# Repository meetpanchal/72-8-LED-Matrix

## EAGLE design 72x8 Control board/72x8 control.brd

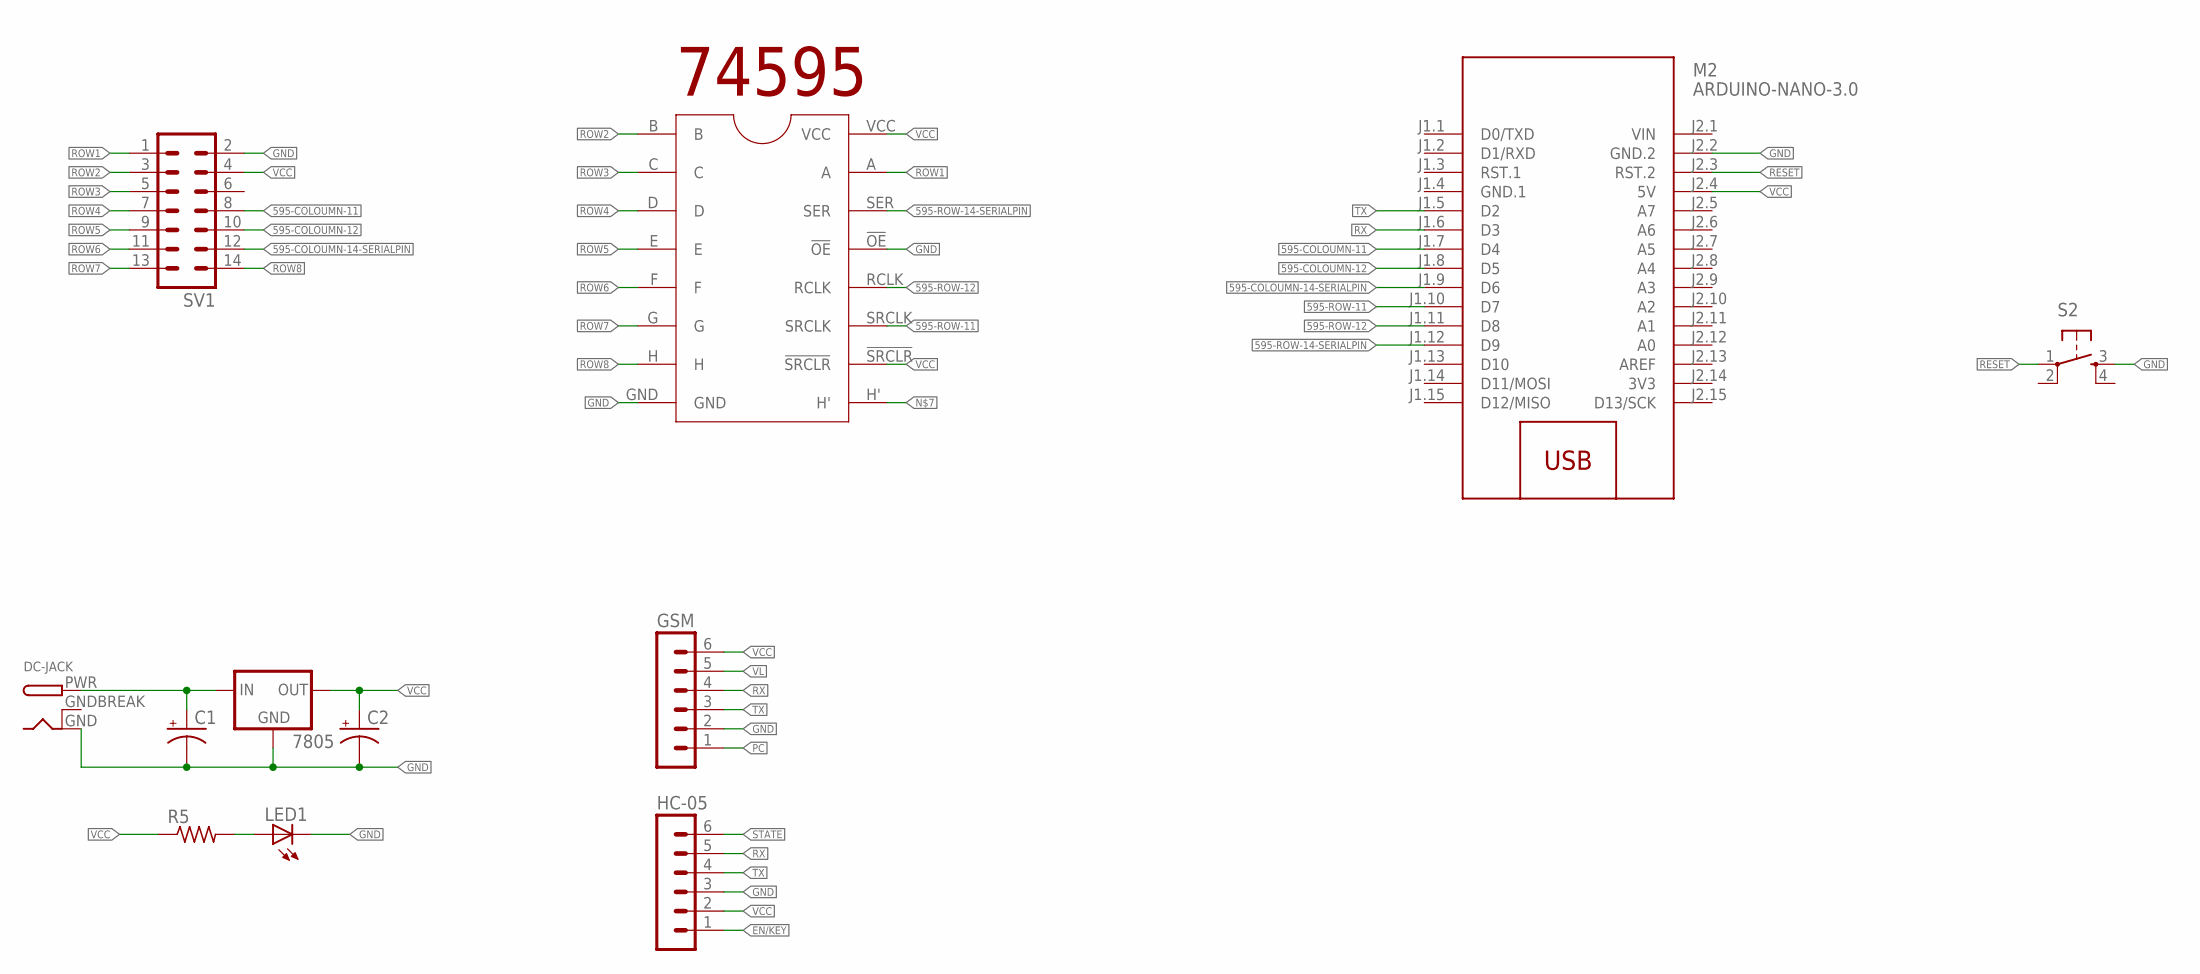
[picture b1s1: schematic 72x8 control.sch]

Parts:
1: 74595; DIL16
7805: 78XX-TO3; TO3-78
C1, C2: CPOL-USE2-5; E2-5
DC-JACK: DCBARRELPTH; DCJACK_2MM_PTH
GSM: MA06-1
HC-05: MA06-1
LED1: LED5MM
M2: ARDUINO-NANO-3.0
R5: R-US_0207/10; 0207/10
S2: TAC_SWITCHPTH; TACTILE-PTH
SV1: MA07-2

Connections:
3V3: M2.J2.14 (3V3)
12V: 7805.2 (IN), C1.+, DC-JACK.PWR
595-COLOUMN-11: M2.J1.7 (D4), SV1.8
595-COLOUMN-12: M2.J1.8 (D5), SV1.10
595-COLOUMN-14-SERIALPIN: M2.J1.9 (D6), SV1.12
595-ROW-11: 1.SRCLK, M2.J1.10 (D7)
595-ROW-12: 1.RCLK, M2.J1.11 (D8)
595-ROW-14-SERIALPIN: 1.SER, M2.J1.12 (D9)
EN/KEY: HC-05.1
GND: 1.!OE, 1.GND, 7805.3 (GND), C1.-, C2.-, DC-JACK.GND, GSM.2, HC-05.3, LED1.K (C), M2.J2.2 (GND.2), S2.3, SV1.2
GND.1: M2.J1.4 (GND.1)
GNDBREAK: DC-JACK.GNDBREAK
unnamed: LED1.A, R5.2
PC: GSM.1
RESET: M2.J2.3 (RST.2), S2.1
ROW1: 1.A, SV1.1
ROW2: 1.B, SV1.3
ROW3: 1.C, SV1.5
ROW4: 1.D, SV1.7
ROW5: 1.E, SV1.9
ROW6: 1.F, SV1.11
ROW7: 1.G, SV1.13
ROW8: 1.H, SV1.14
RX: GSM.4, HC-05.5, M2.J1.6 (D3)
STATE: HC-05.6
TX: GSM.3, HC-05.4, M2.J1.5 (D2)
VCC: 1.!SRCLR, 1.VCC, 7805.1 (OUT), C2.+, GSM.6, HC-05.2, M2.J2.4 (5V), R5.1, SV1.4
VIN: M2.J2.1 (VIN)
VL: GSM.5

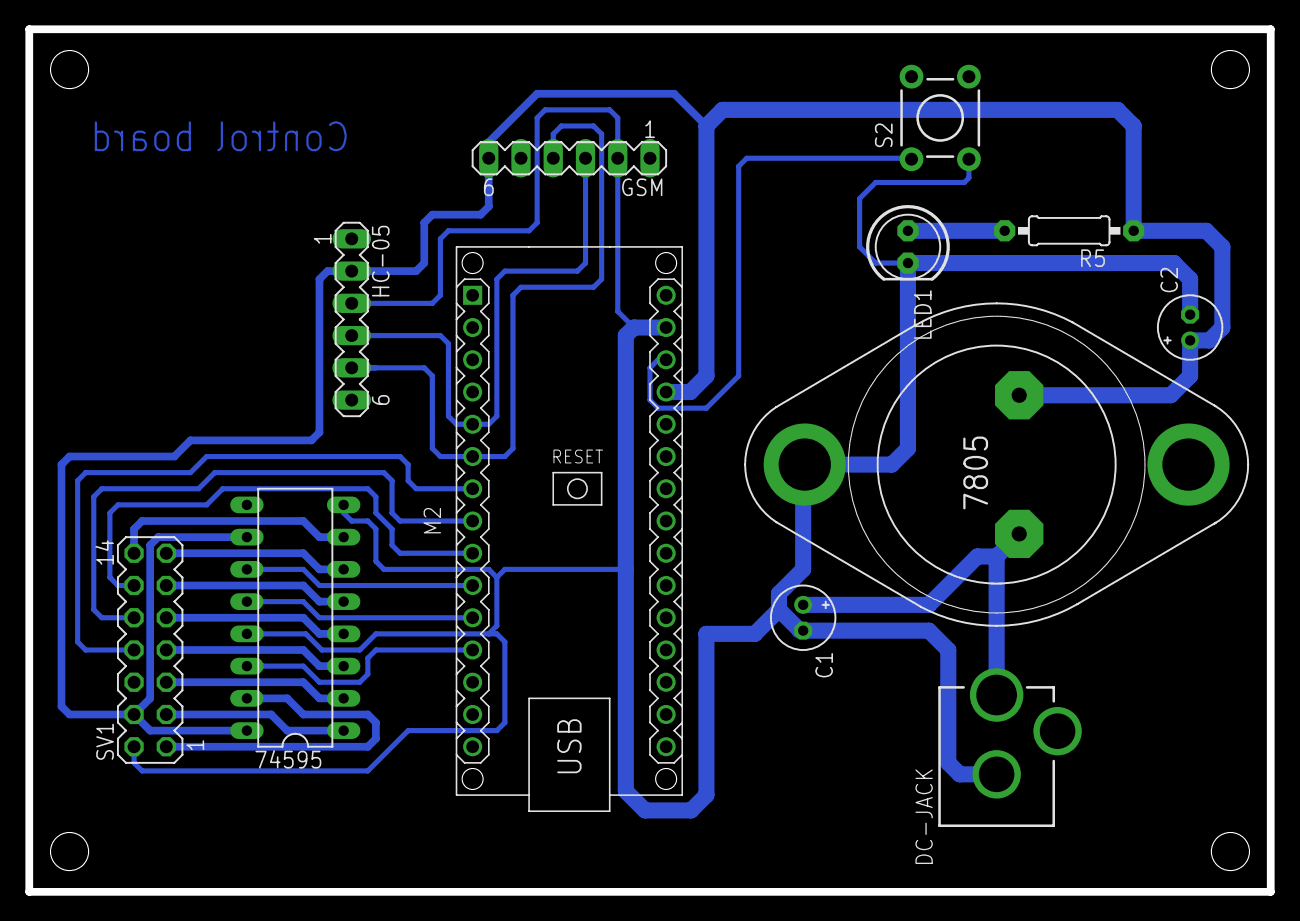
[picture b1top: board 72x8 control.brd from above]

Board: 2 copper layers, 97.8 x 67.9 mm, 12 parts (0 on the bottom side), 21 nets.

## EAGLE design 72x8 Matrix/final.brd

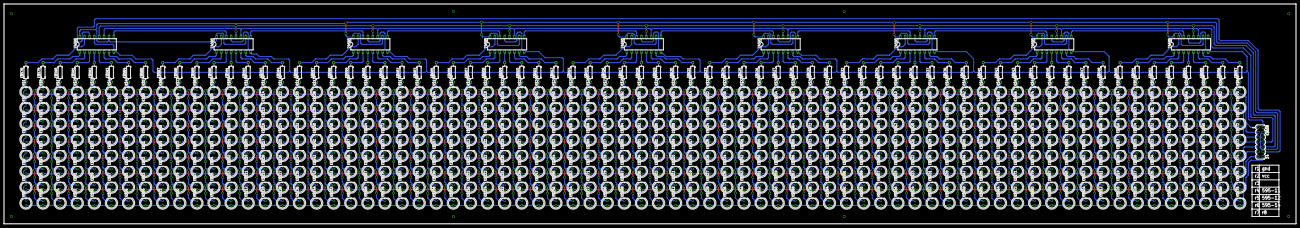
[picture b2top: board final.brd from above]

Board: 2 copper layers, 671.8 x 114.3 mm, 658 parts (0 on the bottom side), 165 nets.

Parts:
E$1, E$2, E$3, E$4, E$5, E$6, E$7, E$8, E$9, E$10, E$11, E$12, E$13, E$14, E$15, E$16, E$17, E$18, E$19, E$20, E$21, E$22, E$23, E$24, E$25, E$26, E$27, E$28, E$29, E$30, E$31, E$32, E$33, E$34, E$35, E$36, E$37, E$38, E$39, E$40, E$41, E$42, E$43, E$44, E$45, E$46, E$47, E$48, E$49, E$50, E$51, E$52, E$53, E$54, E$55, E$56, E$57, E$58, E$59, E$60, E$61, E$62, E$63, E$64, E$65, E$66, E$67, E$68, E$69, E$70, E$71, E$72, E$73, E$74, E$75, E$76, E$77, E$78, E$79, E$80, E$81, E$82, E$83, E$84, E$85, E$86, E$87, E$88, E$89, E$90, E$91, E$92, E$93, E$94, E$95, E$96, E$97, E$98, E$99, E$100, E$101, E$102, E$103, E$104, E$105, E$106, E$107, E$108, E$109, E$110, E$111, E$112, E$113, E$114, E$115, E$116, E$117, E$118, E$119, E$120, E$121, E$122, E$123, E$124, E$125, E$126, E$127, E$128, E$129, E$130, E$131, E$132, E$133, E$134, E$135, E$136, E$137, E$138, E$139, E$140, E$141, E$142, E$143, E$144, E$145, E$146, E$147, E$148, E$149, E$150, E$151, E$152, E$153, E$154, E$155, E$156, E$157, E$158, E$159, E$160, E$161, E$162, E$163, E$164, E$165, E$166, E$167, E$168, E$169, E$170, E$171, E$172, E$173, E$174, E$175, E$176, E$177, E$178, E$179, E$180, E$181, E$182, E$183, E$184, E$185, E$186, E$187, E$188, E$189, E$190, E$191, E$192, E$193, E$194, E$195, E$196, E$197, E$198, E$199, E$200, E$201, E$202, E$203, E$204, E$205, E$206, E$207, E$208, E$209, E$210, E$211, E$212, E$213, E$214, E$215, E$216, E$217, E$218, E$219, E$220, E$221, E$222, E$223, E$224, E$225, E$226, E$227, E$228, E$229, E$230, E$231, E$232, E$233, E$234, E$235, E$236, E$237, E$238, E$239, E$240, E$241, E$242, E$243, E$244, E$245, E$246, E$247, E$248, E$249, E$250, E$251, E$252, E$253, E$254, E$255, E$256, E$257, E$258, E$259, E$260, E$261, E$262, E$263, E$264, E$265, E$266, E$267, E$268, E$269, E$270, E$271, E$272, E$273, E$274, E$275, E$276, E$277, E$278, E$279, E$280, E$281, E$282, E$283, E$284, E$285, E$286, E$287, E$288, E$289, E$290, E$291, E$292, E$293, E$294, E$295, E$296, E$297, E$298, E$299, E$300, E$301, E$302, E$303, E$304, E$305, E$306, E$307, E$308, E$309, E$310, E$311, E$312, E$313, E$314, E$315, E$316, E$317, E$318, E$319, E$320, E$321, E$322, E$323, E$324, E$325, E$326, E$327, E$328, E$329, E$330, E$331, E$332, E$333, E$334, E$335, E$336, E$337, E$338, E$339, E$340, E$341, E$342, E$343, E$344, E$345, E$346, E$347, E$348, E$349, E$350, E$351, E$352, E$353, E$354, E$355, E$356, E$357, E$358, E$359, E$360, E$361, E$362, E$363, E$364, E$365, E$366, E$367, E$368, E$369, E$370, E$371, E$372, E$373, E$374, E$375, E$376, E$377, E$378, E$379, E$380, E$381, E$382, E$383, E$384, E$385, E$386, E$387, E$388, E$389, E$390, E$391, E$392, E$393, E$394, E$395, E$396, E$397, E$398, E$399, E$400, E$401, E$402, E$403, E$404, E$405, E$406, E$407, E$408, E$409, E$410, E$411, E$412, E$413, E$414, E$415, E$416, E$417, E$418, E$419, E$420, E$421, E$422, E$423, E$424, E$425, E$426, E$427, E$428, E$429, E$430, E$431, E$432, E$433, E$434, E$435, E$436, E$437, E$438, E$439, E$440, E$441, E$442, E$443, E$444, E$445, E$446, E$447, E$448, E$449, E$450, E$451, E$452, E$453, E$454, E$455, E$456, E$457, E$458, E$459, E$460, E$461, E$462, E$463, E$464, E$465, E$466, E$467, E$468, E$469, E$470, E$471, E$472, E$473, E$474, E$475, E$476, E$477, E$478, E$479, E$480, E$481, E$482, E$483, E$484, E$485, E$486, E$487, E$488, E$489, E$490, E$491, E$492, E$493, E$494, E$495, E$496, E$497, E$498, E$499, E$500, E$501, E$502, E$503, E$504, E$505, E$506, E$507, E$508, E$509, E$510, E$511, E$512, E$513, E$514, E$515, E$516, E$517, E$518, E$519, E$520, E$521, E$522, E$523, E$524, E$525, E$526, E$527, E$528, E$529, E$530, E$531, E$532, E$533, E$534, E$535, E$536, E$537, E$538, E$539, E$540, E$541, E$542, E$543, E$544, E$545, E$546, E$547, E$548, E$549, E$550, E$551, E$552, E$553, E$554, E$555, E$556, E$557, E$558, E$559, E$560, E$561, E$562, E$563, E$564, E$565, E$566, E$567, E$568, E$569, E$570, E$571, E$572, E$573, E$574, E$575, E$576: LED5MM
E$577, E$586, E$595, E$604, E$613, E$622, E$631, E$640, E$649: DIL16
E$578, E$579, E$580, E$581, E$582, E$583, E$584, E$585, E$587, E$588, E$589, E$590, E$591, E$592, E$593, E$594, E$596, E$597, E$598, E$599, E$600, E$601, E$602, E$603, E$605, E$606, E$607, E$608, E$609, E$610, E$611, E$612, E$614, E$615, E$616, E$617, E$618, E$619, E$620, E$621, E$623, E$624, E$625, E$626, E$627, E$628, E$629, E$630, E$632, E$633, E$634, E$635, E$636, E$637, E$638, E$639, E$641, E$642, E$643, E$644, E$645, E$646, E$647, E$648, E$650, E$651, E$652, E$653, E$654, E$655, E$656, E$657: 0207/10
E$658: MA07-2

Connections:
595-11: E$577.SRCLK, E$586.SRCLK, E$595.SRCLK, E$604.SRCLK, E$613.SRCLK, E$622.SRCLK, E$631.SRCLK, E$640.SRCLK, E$649.SRCLK, E$658.8
595-12: E$577.RCLK, E$586.RCLK, E$595.RCLK, E$604.RCLK, E$613.RCLK, E$622.RCLK, E$631.RCLK, E$640.RCLK, E$649.RCLK, E$658.10
595-(14)-SERIALPIN: E$577.SER, E$658.12
GND: E$577.!OE, E$577.GND, E$586.!OE, E$586.GND, E$595.!OE, E$595.GND, E$604.!OE, E$604.GND, E$613.!OE, E$613.GND, E$622.!OE, E$622.GND, E$631.!OE, E$631.GND, E$640.!OE, E$640.GND, E$649.!OE, E$649.GND, E$658.2
ROW1: E$1.A, E$9.A, E$17.A, E$25.A, E$33.A, E$41.A, E$49.A, E$57.A, E$65.A, E$73.A, E$81.A, E$89.A, E$97.A, E$105.A, E$113.A, E$121.A, E$129.A, E$137.A, E$145.A, E$153.A, E$161.A, E$169.A, E$177.A, E$185.A, E$193.A, E$201.A, E$209.A, E$217.A, E$225.A, E$233.A, E$241.A, E$249.A, E$257.A, E$265.A, E$273.A, E$281.A, E$289.A, E$297.A, E$305.A, E$313.A, E$321.A, E$329.A, E$337.A, E$345.A, E$353.A, E$361.A, E$369.A, E$377.A, E$385.A, E$393.A, E$401.A, E$409.A, E$417.A, E$425.A, E$433.A, E$441.A, E$449.A, E$457.A, E$465.A, E$473.A, E$481.A, E$489.A, E$497.A, E$505.A, E$513.A, E$521.A, E$529.A, E$537.A, E$545.A, E$553.A, E$561.A, E$569.A, E$658.1
ROW2: E$2.A, E$10.A, E$18.A, E$26.A, E$34.A, E$42.A, E$50.A, E$58.A, E$66.A, E$74.A, E$82.A, E$90.A, E$98.A, E$106.A, E$114.A, E$122.A, E$130.A, E$138.A, E$146.A, E$154.A, E$162.A, E$170.A, E$178.A, E$186.A, E$194.A, E$202.A, E$210.A, E$218.A, E$226.A, E$234.A, E$242.A, E$250.A, E$258.A, E$266.A, E$274.A, E$282.A, E$290.A, E$298.A, E$306.A, E$314.A, E$322.A, E$330.A, E$338.A, E$346.A, E$354.A, E$362.A, E$370.A, E$378.A, E$386.A, E$394.A, E$402.A, E$410.A, E$418.A, E$426.A, E$434.A, E$442.A, E$450.A, E$458.A, E$466.A, E$474.A, E$482.A, E$490.A, E$498.A, E$506.A, E$514.A, E$522.A, E$530.A, E$538.A, E$546.A, E$554.A, E$562.A, E$570.A, E$658.3
ROW3: E$3.A, E$11.A, E$19.A, E$27.A, E$35.A, E$43.A, E$51.A, E$59.A, E$67.A, E$75.A, E$83.A, E$91.A, E$99.A, E$107.A, E$115.A, E$123.A, E$131.A, E$139.A, E$147.A, E$155.A, E$163.A, E$171.A, E$179.A, E$187.A, E$195.A, E$203.A, E$211.A, E$219.A, E$227.A, E$235.A, E$243.A, E$251.A, E$259.A, E$267.A, E$275.A, E$283.A, E$291.A, E$299.A, E$307.A, E$315.A, E$323.A, E$331.A, E$339.A, E$347.A, E$355.A, E$363.A, E$371.A, E$379.A, E$387.A, E$395.A, E$403.A, E$411.A, E$419.A, E$427.A, E$435.A, E$443.A, E$451.A, E$459.A, E$467.A, E$475.A, E$483.A, E$491.A, E$499.A, E$507.A, E$515.A, E$523.A, E$531.A, E$539.A, E$547.A, E$555.A, E$563.A, E$571.A, E$658.5
ROW4: E$4.A, E$12.A, E$20.A, E$28.A, E$36.A, E$44.A, E$52.A, E$60.A, E$68.A, E$76.A, E$84.A, E$92.A, E$100.A, E$108.A, E$116.A, E$124.A, E$132.A, E$140.A, E$148.A, E$156.A, E$164.A, E$172.A, E$180.A, E$188.A, E$196.A, E$204.A, E$212.A, E$220.A, E$228.A, E$236.A, E$244.A, E$252.A, E$260.A, E$268.A, E$276.A, E$284.A, E$292.A, E$300.A, E$308.A, E$316.A, E$324.A, E$332.A, E$340.A, E$348.A, E$356.A, E$364.A, E$372.A, E$380.A, E$388.A, E$396.A, E$404.A, E$412.A, E$420.A, E$428.A, E$436.A, E$444.A, E$452.A, E$460.A, E$468.A, E$476.A, E$484.A, E$492.A, E$500.A, E$508.A, E$516.A, E$524.A, E$532.A, E$540.A, E$548.A, E$556.A, E$564.A, E$572.A, E$658.7
ROW5: E$5.A, E$13.A, E$21.A, E$29.A, E$37.A, E$45.A, E$53.A, E$61.A, E$69.A, E$77.A, E$85.A, E$93.A, E$101.A, E$109.A, E$117.A, E$125.A, E$133.A, E$141.A, E$149.A, E$157.A, E$165.A, E$173.A, E$181.A, E$189.A, E$197.A, E$205.A, E$213.A, E$221.A, E$229.A, E$237.A, E$245.A, E$253.A, E$261.A, E$269.A, E$277.A, E$285.A, E$293.A, E$301.A, E$309.A, E$317.A, E$325.A, E$333.A, E$341.A, E$349.A, E$357.A, E$365.A, E$373.A, E$381.A, E$389.A, E$397.A, E$405.A, E$413.A, E$421.A, E$429.A, E$437.A, E$445.A, E$453.A, E$461.A, E$469.A, E$477.A, E$485.A, E$493.A, E$501.A, E$509.A, E$517.A, E$525.A, E$533.A, E$541.A, E$549.A, E$557.A, E$565.A, E$573.A, E$658.9
ROW6: E$6.A, E$14.A, E$22.A, E$30.A, E$38.A, E$46.A, E$54.A, E$62.A, E$70.A, E$78.A, E$86.A, E$94.A, E$102.A, E$110.A, E$118.A, E$126.A, E$134.A, E$142.A, E$150.A, E$158.A, E$166.A, E$174.A, E$182.A, E$190.A, E$198.A, E$206.A, E$214.A, E$222.A, E$230.A, E$238.A, E$246.A, E$254.A, E$262.A, E$270.A, E$278.A, E$286.A, E$294.A, E$302.A, E$310.A, E$318.A, E$326.A, E$334.A, E$342.A, E$350.A, E$358.A, E$366.A, E$374.A, E$382.A, E$390.A, E$398.A, E$406.A, E$414.A, E$422.A, E$430.A, E$438.A, E$446.A, E$454.A, E$462.A, E$470.A, E$478.A, E$486.A, E$494.A, E$502.A, E$510.A, E$518.A, E$526.A, E$534.A, E$542.A, E$550.A, E$558.A, E$566.A, E$574.A, E$658.11
ROW7: E$7.A, E$15.A, E$23.A, E$31.A, E$39.A, E$47.A, E$55.A, E$63.A, E$71.A, E$79.A, E$87.A, E$95.A, E$103.A, E$111.A, E$119.A, E$127.A, E$135.A, E$143.A, E$151.A, E$159.A, E$167.A, E$175.A, E$183.A, E$191.A, E$199.A, E$207.A, E$215.A, E$223.A, E$231.A, E$239.A, E$247.A, E$255.A, E$263.A, E$271.A, E$279.A, E$287.A, E$295.A, E$303.A, E$311.A, E$319.A, E$327.A, E$335.A, E$343.A, E$351.A, E$359.A, E$367.A, E$375.A, E$383.A, E$391.A, E$399.A, E$407.A, E$415.A, E$423.A, E$431.A, E$439.A, E$447.A, E$455.A, E$463.A, E$471.A, E$479.A, E$487.A, E$495.A, E$503.A, E$511.A, E$519.A, E$527.A, E$535.A, E$543.A, E$551.A, E$559.A, E$567.A, E$575.A, E$658.13
ROW8: E$8.A, E$16.A, E$24.A, E$32.A, E$40.A, E$48.A, E$56.A, E$64.A, E$72.A, E$80.A, E$88.A, E$96.A, E$104.A, E$112.A, E$120.A, E$128.A, E$136.A, E$144.A, E$152.A, E$160.A, E$168.A, E$176.A, E$184.A, E$192.A, E$200.A, E$208.A, E$216.A, E$224.A, E$232.A, E$240.A, E$248.A, E$256.A, E$264.A, E$272.A, E$280.A, E$288.A, E$296.A, E$304.A, E$312.A, E$320.A, E$328.A, E$336.A, E$344.A, E$352.A, E$360.A, E$368.A, E$376.A, E$384.A, E$392.A, E$400.A, E$408.A, E$416.A, E$424.A, E$432.A, E$440.A, E$448.A, E$456.A, E$464.A, E$472.A, E$480.A, E$488.A, E$496.A, E$504.A, E$512.A, E$520.A, E$528.A, E$536.A, E$544.A, E$552.A, E$560.A, E$568.A, E$576.A, E$658.14
S$1: E$9.K, E$10.K, E$11.K, E$12.K, E$13.K, E$14.K, E$15.K, E$16.K, E$579.1
S$10: E$17.K, E$18.K, E$19.K, E$20.K, E$21.K, E$22.K, E$23.K, E$24.K, E$580.1
S$11: E$1.K, E$2.K, E$3.K, E$4.K, E$5.K, E$6.K, E$7.K, E$8.K, E$578.1
S$12: E$577.A, E$578.2
S$13: E$577.B, E$579.2
S$14: E$577.C, E$580.2
S$15: E$577.D, E$581.2
S$16: E$577.E, E$582.2
S$17: E$577.F, E$583.2
S$18: E$577.G, E$584.2
S$19: E$25.K, E$26.K, E$27.K, E$28.K, E$29.K, E$30.K, E$31.K, E$32.K, E$581.1
S$20: E$41.K, E$42.K, E$43.K, E$44.K, E$45.K, E$46.K, E$47.K, E$48.K, E$583.1
S$21: E$57.K, E$58.K, E$59.K, E$60.K, E$61.K, E$62.K, E$63.K, E$64.K, E$585.1
S$22: E$49.K, E$50.K, E$51.K, E$52.K, E$53.K, E$54.K, E$55.K, E$56.K, E$584.1
S$23: E$33.K, E$34.K, E$35.K, E$36.K, E$37.K, E$38.K, E$39.K, E$40.K, E$582.1
S$24: E$73.K, E$74.K, E$75.K, E$76.K, E$77.K, E$78.K, E$79.K, E$80.K, E$588.1
S$25: E$89.K, E$90.K, E$91.K, E$92.K, E$93.K, E$94.K, E$95.K, E$96.K, E$590.1
S$26: E$81.K, E$82.K, E$83.K, E$84.K, E$85.K, E$86.K, E$87.K, E$88.K, E$589.1
S$27: E$105.K, E$106.K, E$107.K, E$108.K, E$109.K, E$110.K, E$111.K, E$112.K, E$592.1
S$28: E$121.K, E$122.K, E$123.K, E$124.K, E$125.K, E$126.K, E$127.K, E$128.K, E$594.1
S$29: E$113.K, E$114.K, E$115.K, E$116.K, E$117.K, E$118.K, E$119.K, E$120.K, E$593.1
S$30: E$97.K, E$98.K, E$99.K, E$100.K, E$101.K, E$102.K, E$103.K, E$104.K, E$591.1
S$31: E$65.K, E$66.K, E$67.K, E$68.K, E$69.K, E$70.K, E$71.K, E$72.K, E$587.1
S$32: E$137.K, E$138.K, E$139.K, E$140.K, E$141.K, E$142.K, E$143.K, E$144.K, E$597.1
S$33: E$153.K, E$154.K, E$155.K, E$156.K, E$157.K, E$158.K, E$159.K, E$160.K, E$599.1
S$34: E$145.K, E$146.K, E$147.K, E$148.K, E$149.K, E$150.K, E$151.K, E$152.K, E$598.1
S$35: E$169.K, E$170.K, E$171.K, E$172.K, E$173.K, E$174.K, E$175.K, E$176.K, E$601.1
S$36: E$185.K, E$186.K, E$187.K, E$188.K, E$189.K, E$190.K, E$191.K, E$192.K, E$603.1
S$37: E$177.K, E$178.K, E$179.K, E$180.K, E$181.K, E$182.K, E$183.K, E$184.K, E$602.1
S$38: E$161.K, E$162.K, E$163.K, E$164.K, E$165.K, E$166.K, E$167.K, E$168.K, E$600.1
S$39: E$201.K, E$202.K, E$203.K, E$204.K, E$205.K, E$206.K, E$207.K, E$208.K, E$606.1
S$40: E$217.K, E$218.K, E$219.K, E$220.K, E$221.K, E$222.K, E$223.K, E$224.K, E$608.1
S$41: E$209.K, E$210.K, E$211.K, E$212.K, E$213.K, E$214.K, E$215.K, E$216.K, E$607.1
S$42: E$233.K, E$234.K, E$235.K, E$236.K, E$237.K, E$238.K, E$239.K, E$240.K, E$610.1
S$43: E$249.K, E$250.K, E$251.K, E$252.K, E$253.K, E$254.K, E$255.K, E$256.K, E$612.1
S$44: E$241.K, E$242.K, E$243.K, E$244.K, E$245.K, E$246.K, E$247.K, E$248.K, E$611.1
S$45: E$225.K, E$226.K, E$227.K, E$228.K, E$229.K, E$230.K, E$231.K, E$232.K, E$609.1
S$46: E$193.K, E$194.K, E$195.K, E$196.K, E$197.K, E$198.K, E$199.K, E$200.K, E$605.1
S$47: E$129.K, E$130.K, E$131.K, E$132.K, E$133.K, E$134.K, E$135.K, E$136.K, E$596.1
S$48: E$265.K, E$266.K, E$267.K, E$268.K, E$269.K, E$270.K, E$271.K, E$272.K, E$615.1
S$49: E$281.K, E$282.K, E$283.K, E$284.K, E$285.K, E$286.K, E$287.K, E$288.K, E$617.1
S$50: E$273.K, E$274.K, E$275.K, E$276.K, E$277.K, E$278.K, E$279.K, E$280.K, E$616.1
S$51: E$297.K, E$298.K, E$299.K, E$300.K, E$301.K, E$302.K, E$303.K, E$304.K, E$619.1
S$52: E$313.K, E$314.K, E$315.K, E$316.K, E$317.K, E$318.K, E$319.K, E$320.K, E$621.1
S$53: E$305.K, E$306.K, E$307.K, E$308.K, E$309.K, E$310.K, E$311.K, E$312.K, E$620.1
S$54: E$289.K, E$290.K, E$291.K, E$292.K, E$293.K, E$294.K, E$295.K, E$296.K, E$618.1
S$55: E$329.K, E$330.K, E$331.K, E$332.K, E$333.K, E$334.K, E$335.K, E$336.K, E$624.1
S$56: E$345.K, E$346.K, E$347.K, E$348.K, E$349.K, E$350.K, E$351.K, E$352.K, E$626.1
S$57: E$337.K, E$338.K, E$339.K, E$340.K, E$341.K, E$342.K, E$343.K, E$344.K, E$625.1
S$58: E$361.K, E$362.K, E$363.K, E$364.K, E$365.K, E$366.K, E$367.K, E$368.K, E$628.1
S$59: E$377.K, E$378.K, E$379.K, E$380.K, E$381.K, E$382.K, E$383.K, E$384.K, E$630.1
S$60: E$369.K, E$370.K, E$371.K, E$372.K, E$373.K, E$374.K, E$375.K, E$376.K, E$629.1
S$61: E$353.K, E$354.K, E$355.K, E$356.K, E$357.K, E$358.K, E$359.K, E$360.K, E$627.1
S$62: E$321.K, E$322.K, E$323.K, E$324.K, E$325.K, E$326.K, E$327.K, E$328.K, E$623.1
S$63: E$393.K, E$394.K, E$395.K, E$396.K, E$397.K, E$398.K, E$399.K, E$400.K, E$633.1
S$64: E$409.K, E$410.K, E$411.K, E$412.K, E$413.K, E$414.K, E$415.K, E$416.K, E$635.1
S$65: E$401.K, E$402.K, E$403.K, E$404.K, E$405.K, E$406.K, E$407.K, E$408.K, E$634.1
S$66: E$425.K, E$426.K, E$427.K, E$428.K, E$429.K, E$430.K, E$431.K, E$432.K, E$637.1
S$67: E$441.K, E$442.K, E$443.K, E$444.K, E$445.K, E$446.K, E$447.K, E$448.K, E$639.1
S$68: E$433.K, E$434.K, E$435.K, E$436.K, E$437.K, E$438.K, E$439.K, E$440.K, E$638.1
S$69: E$417.K, E$418.K, E$419.K, E$420.K, E$421.K, E$422.K, E$423.K, E$424.K, E$636.1
S$70: E$457.K, E$458.K, E$459.K, E$460.K, E$461.K, E$462.K, E$463.K, E$464.K, E$642.1
S$71: E$473.K, E$474.K, E$475.K, E$476.K, E$477.K, E$478.K, E$479.K, E$480.K, E$644.1
S$72: E$465.K, E$466.K, E$467.K, E$468.K, E$469.K, E$470.K, E$471.K, E$472.K, E$643.1
S$73: E$489.K, E$490.K, E$491.K, E$492.K, E$493.K, E$494.K, E$495.K, E$496.K, E$646.1
S$74: E$505.K, E$506.K, E$507.K, E$508.K, E$509.K, E$510.K, E$511.K, E$512.K, E$648.1
S$75: E$497.K, E$498.K, E$499.K, E$500.K, E$501.K, E$502.K, E$503.K, E$504.K, E$647.1
S$76: E$481.K, E$482.K, E$483.K, E$484.K, E$485.K, E$486.K, E$487.K, E$488.K, E$645.1
S$77: E$449.K, E$450.K, E$451.K, E$452.K, E$453.K, E$454.K, E$455.K, E$456.K, E$641.1
S$78: E$385.K, E$386.K, E$387.K, E$388.K, E$389.K, E$390.K, E$391.K, E$392.K, E$632.1
S$79: E$257.K, E$258.K, E$259.K, E$260.K, E$261.K, E$262.K, E$263.K, E$264.K, E$614.1
S$80: E$521.K, E$522.K, E$523.K, E$524.K, E$525.K, E$526.K, E$527.K, E$528.K, E$651.1
S$81: E$537.K, E$538.K, E$539.K, E$540.K, E$541.K, E$542.K, E$543.K, E$544.K, E$653.1
S$82: E$529.K, E$530.K, E$531.K, E$532.K, E$533.K, E$534.K, E$535.K, E$536.K, E$652.1
S$83: E$553.K, E$554.K, E$555.K, E$556.K, E$557.K, E$558.K, E$559.K, E$560.K, E$655.1
S$84: E$569.K, E$570.K, E$571.K, E$572.K, E$573.K, E$574.K, E$575.K, E$576.K, E$657.1
S$85: E$561.K, E$562.K, E$563.K, E$564.K, E$565.K, E$566.K, E$567.K, E$568.K, E$656.1
S$86: E$545.K, E$546.K, E$547.K, E$548.K, E$549.K, E$550.K, E$551.K, E$552.K, E$654.1
S$87: E$513.K, E$514.K, E$515.K, E$516.K, E$517.K, E$518.K, E$519.K, E$520.K, E$650.1
S$88: E$577.H, E$585.2
S$89: E$586.A, E$587.2
S$90: E$586.B, E$588.2
S$91: E$586.C, E$589.2
S$92: E$586.D, E$590.2
S$93: E$586.E, E$591.2
S$94: E$586.F, E$592.2
S$95: E$586.G, E$593.2
S$96: E$586.H, E$594.2
S$97: E$595.A, E$596.2
S$98: E$595.B, E$597.2
S$99: E$595.C, E$598.2
S$100: E$595.D, E$599.2
S$101: E$595.E, E$600.2
S$102: E$595.F, E$601.2
S$103: E$595.G, E$602.2
S$104: E$595.H, E$603.2
S$105: E$604.A, E$605.2
S$106: E$604.B, E$606.2
S$107: E$604.C, E$607.2
S$108: E$604.D, E$608.2
S$109: E$604.E, E$609.2
S$110: E$604.F, E$610.2
S$111: E$604.G, E$611.2
S$112: E$604.H, E$612.2
S$113: E$613.A, E$614.2
S$114: E$613.B, E$615.2
S$115: E$613.C, E$616.2
S$116: E$613.D, E$617.2
S$117: E$613.E, E$618.2
S$118: E$613.F, E$619.2
S$119: E$613.G, E$620.2
S$120: E$613.H, E$621.2
S$121: E$622.A, E$623.2
S$122: E$622.B, E$624.2
S$123: E$622.C, E$625.2
S$124: E$622.D, E$626.2
S$125: E$622.E, E$627.2
S$126: E$622.F, E$628.2
S$127: E$622.G, E$629.2
S$128: E$622.H, E$630.2
S$129: E$631.A, E$632.2
S$130: E$631.B, E$633.2
S$131: E$631.C, E$634.2
S$132: E$631.D, E$635.2
S$133: E$631.E, E$636.2
S$134: E$631.F, E$637.2
S$135: E$631.G, E$638.2
S$136: E$631.H, E$639.2
S$137: E$640.A, E$641.2
S$138: E$640.B, E$642.2
S$139: E$640.C, E$643.2
S$140: E$640.D, E$644.2
S$141: E$640.E, E$645.2
S$142: E$640.F, E$646.2
S$143: E$640.G, E$647.2
S$144: E$640.H, E$648.2
S$145: E$649.A, E$650.2
S$146: E$649.B, E$651.2
S$147: E$649.C, E$652.2
S$148: E$649.D, E$653.2
S$149: E$649.E, E$654.2
S$150: E$649.F, E$655.2
S$151: E$649.G, E$656.2
S$152: E$649.H, E$657.2
S$155: E$577.H', E$586.SER
S$156: E$586.H', E$595.SER
S$157: E$595.H', E$604.SER
S$158: E$604.H', E$613.SER
S$159: E$613.H', E$622.SER
S$160: E$622.H', E$631.SER
S$161: E$631.H', E$640.SER
S$162: E$640.H', E$649.SER
VCC: E$577.!SRCLR, E$577.VCC, E$586.!SRCLR, E$586.VCC, E$595.!SRCLR, E$595.VCC, E$604.!SRCLR, E$604.VCC, E$613.!SRCLR, E$613.VCC, E$622.!SRCLR, E$622.VCC, E$631.!SRCLR, E$631.VCC, E$640.!SRCLR, E$640.VCC, E$649.!SRCLR, E$649.VCC, E$658.4

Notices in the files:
parts and their libraries:
DIY-Modules: Released under the Creative Commons Attribution 4.0 International License: http://creativecommons.org/licenses/by/4.0
SparkFun-Retired: Licensing: Creative Commons ShareAlike 4.0 International - https://creativecommons.org/licenses/by-sa/4.0
